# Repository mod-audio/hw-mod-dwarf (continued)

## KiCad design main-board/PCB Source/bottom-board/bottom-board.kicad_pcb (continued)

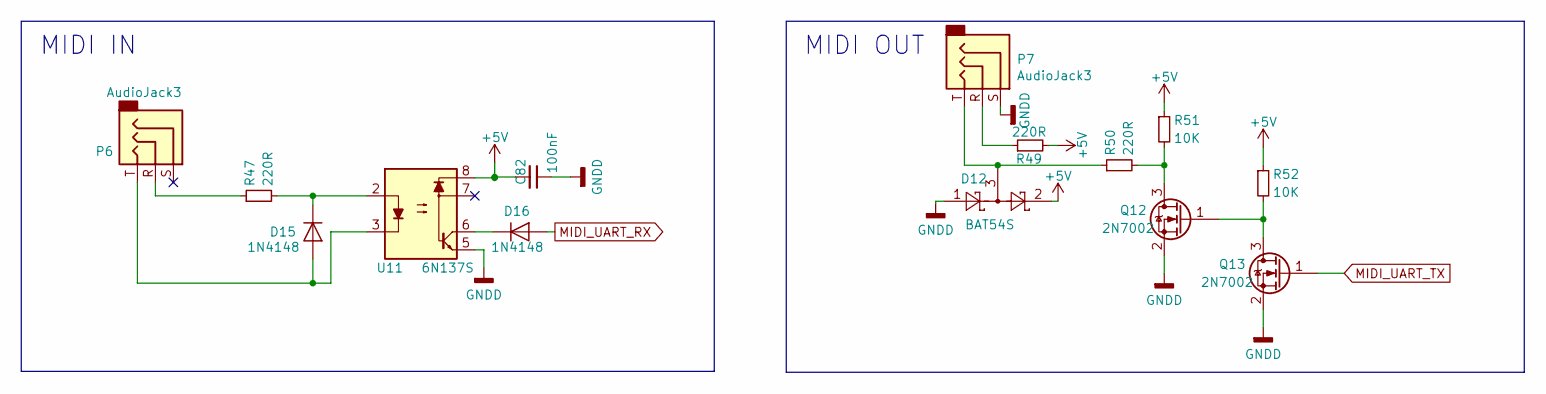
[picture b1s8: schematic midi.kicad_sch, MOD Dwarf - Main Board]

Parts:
C82: 100nF; C_0603_1608Metric; MPN GCM188R71C104KA37D
D12: BAT54S; SOT-23; MPN BAT54SFILM
D15, D16: 1N4148; D_SOD-323; MPN 1N4148WS
P6, P7: AudioJack3; Jack_3.5mm_CUI_SJ-3523-SMT_Horizontal; MPN SJ-3523-SMT-TR
Q12, Q13: 2N7002; SOT-23; MPN 2N7002P,215
R47, R49, R50: 220R; R_0603_1608Metric; MPN RC0603FR-07220RL
R51, R52: 10K; R_0603_1608Metric; MPN RR0816P-103-D
U11: 6N137S; MPN 6N137S

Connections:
+5V: C82.2, D12.2, R49.2, R51.1, R52.1, U11.8; also elsewhere on the board
GNDD: C82.1, D12.1, P7.S, Q12.2 (S), Q13.2 (S), U11.5; also elsewhere on the board
MIDI_UART_RX: D16.2 (A); also elsewhere on the board
MIDI_UART_TX: Q13.1 (G); also elsewhere on the board
unnamed: D12.3, P7.T, R50.1
unnamed: D15.1 (K), R47.2, U11.2
unnamed: D15.2 (A), P6.T, U11.3
unnamed: D16.1 (K), U11.6
unnamed: P6.R, R47.1
unnamed: P7.R, R49.1
unnamed: Q12.1 (G), Q13.3 (D), R52.2
unnamed: Q12.3 (D), R50.2, R51.2

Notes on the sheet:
MIDI OUT
MIDI IN

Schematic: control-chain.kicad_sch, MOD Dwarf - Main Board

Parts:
C54, C62: 100nF; C_0603_1608Metric; MPN GCM188R71C104KA37D
C61: 10uF; CP_Elec_4x5.7; MPN EEE-HB1C100R
P13: RJ45; Ethernet_Jack_54602-908LF; MPN 54602-908LF
R55, R56, R63: 100R; R_0603_1608Metric; MPN RT0603DRD07100RL
R57, R58: 10K; R_0603_1608Metric; MPN RR0816P-103-D
R59, R60, R61, R62: 56R; R_0603_1608Metric; MPN CRGCQ0603F56R
U12: ISL83491; SOIC-14_3.9x8.7mm_P1.27mm; MPN ISL83491IBZ

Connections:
+12V: C61.1, C62.1, P13.4, P13.5; also elsewhere on the board
CHAIN_UART_DE: R58.1, U12.4 (DE); also elsewhere on the board
CHAIN_UART_RE: R57.2, U12.3 (~RE); also elsewhere on the board
CHAIN_UART_RX: R56.2; also elsewhere on the board
CHAIN_UART_TX: R55.2; also elsewhere on the board
GNDD: C54.2, C61.2, C62.2, P13.7, P13.8, R58.2, U12.6 (GND), U12.7 (GND); also elsewhere on the board
unnamed: R55.1, U12.5 (DI)
unnamed: R56.1, U12.2 (RO)
unnamed: R59.2, U12.12 (A)
unnamed: R60.2, U12.11 (~B)
unnamed: R61.2, U12.9 (Y)
unnamed: R62.2, U12.10 (~Z)
RS485_RX+: P13.3, R59.1, R63.1
RS485_RX-: P13.6, R60.1, R63.2
RS485_TX+: P13.1, R61.1
RS485_TX-: P13.2, R62.1

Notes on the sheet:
This port is NOT used for ethernet, but for a serial protocol that includes power over the RJ-45 connector

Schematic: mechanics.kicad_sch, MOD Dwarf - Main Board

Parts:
FID1, FID2, FID3: FIDUCIAL; fiducial_in-circuit
H1, H2, H3, H4: HOLE; Hole_3.5mm
H6, H7: MountingHole_Pad; MountingHole_3.2mm_M3_DIN965_Pad; MPN 9774030243R

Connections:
GNDD: H6.1, H7.1; also elsewhere on the board

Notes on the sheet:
SOM Mounting holes

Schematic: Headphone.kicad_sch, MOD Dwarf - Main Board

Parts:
C63, C64, C65, C66: 10uF; CP_Elec_4x5.7; MPN EEE-HB1C100R
C67, C69: 10uF; C_0805_2012Metric; MPN GRM219R61E106KA12D
C68, C85, C86: 100nF; C_0603_1608Metric; MPN GCM188R71C104KA37D
C70, C71: 100uF; CP_Elec_6.3x7.7; MPN 107SML016M
D17, D18: BAT54S; SOT-23; MPN BAT54SFILM
P14: AudioJack3; Jack_3.5mm_CUI_SJ-3523-SMT_Horizontal; MPN SJ-3523-SMT-TR
Q9, Q10: MMBFJ110; SOT-23; MPN MMBFJ110
R90, R91: 1M 1%; R_0603_1608Metric; MPN RT0603BRD071ML
R92, R93: 56K; R_0603_1608Metric; MPN RMCF0603FT56K0
R94, R95: 22R; R_0603_1608Metric; MPN RMCF0603JT22R0
R96, R97: 75K 1%; R_0603_1608Metric; MPN RR0816P-753-D
R103, R104: 6R8; R_0603_1608Metric; MPN RMCF0603FT6R80
R110, R111: 1M 1%; R_0603_1608Metric; MPN DO NOT PLACE
U8: LM4811; TSSOP-10_3x3mm_P0.5mm; MPN LM4811MM/NOPB

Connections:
+5VA: C67.2, C68.1, D17.2, D18.2, Q9.1 (D), Q10.1 (D), R110.2, R111.2, U8.10 (VDD); also elsewhere on the board
CODEC_DAC_A: C63.1; also elsewhere on the board
CODEC_DAC_B: C64.1; also elsewhere on the board
GNDA: C67.1, C68.2, C69.2, C85.1, C86.1, D17.1, D18.1, P14.S, R90.1, R91.1, R92.1, R93.1, R96.1, R97.1, U8.5 (GND), U8.7 (SHDN); also elsewhere on the board
HP_CLOCK: R95.1; also elsewhere on the board
HP_VOL: R94.1; also elsewhere on the board
unnamed: C63.2, Q9.3 (G), R90.2, R111.1
unnamed: C64.2, Q10.3 (G), R91.2, R110.1
unnamed: C65.1, Q9.2 (S), R92.2
unnamed: C65.2, U8.8 (VIN2)
unnamed: C66.1, Q10.2 (S), R93.2
unnamed: C66.2, U8.2 (VIN1)
unnamed: C69.1, U8.3 (BYPASS)
unnamed: C70.1, C85.2, D17.3, U8.1 (VOUT1)
unnamed: C70.2, R96.2, R103.2
unnamed: C71.1, C86.2, D18.3, U8.9 (VOUT2)
unnamed: C71.2, R97.2, R104.1
unnamed: P14.R, R104.2
unnamed: P14.T, R103.1
unnamed: R94.2, U8.6 (UP/DN)
unnamed: R95.2, U8.4 (CLOCK)

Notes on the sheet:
Max power 105mW
LM4811 has adjustable gain of -33dB to +12dB, this is applied to the main out signal
Minimal load of 16 ohm with 0.1% THD+N

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
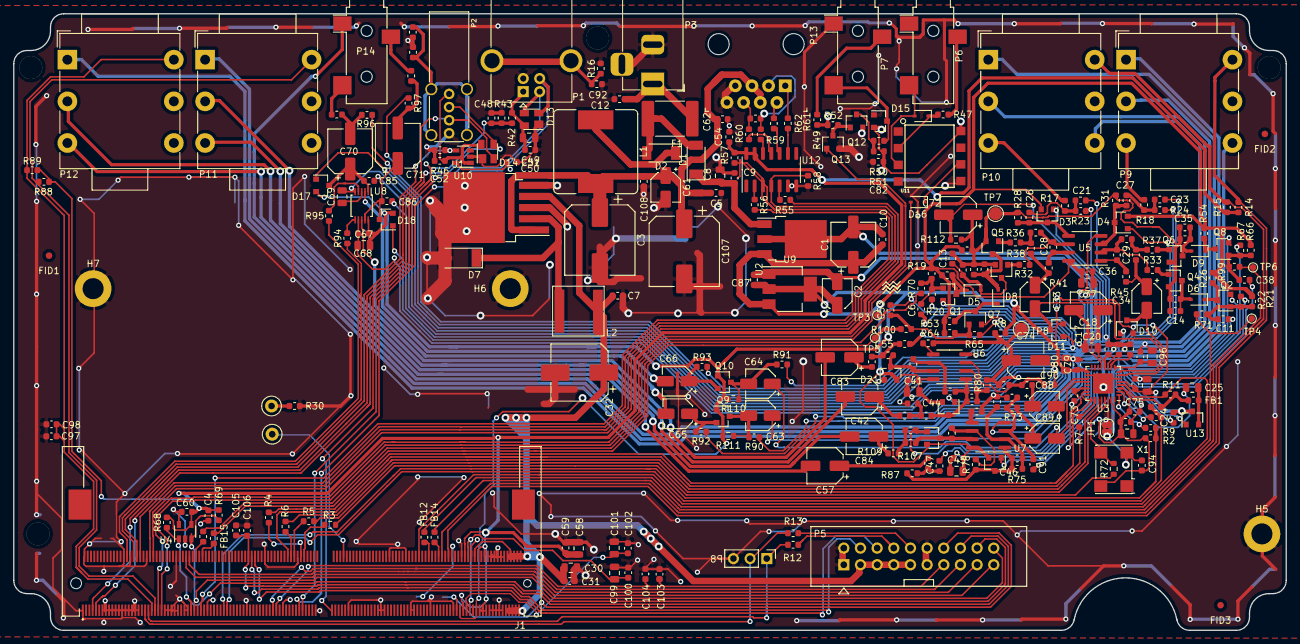
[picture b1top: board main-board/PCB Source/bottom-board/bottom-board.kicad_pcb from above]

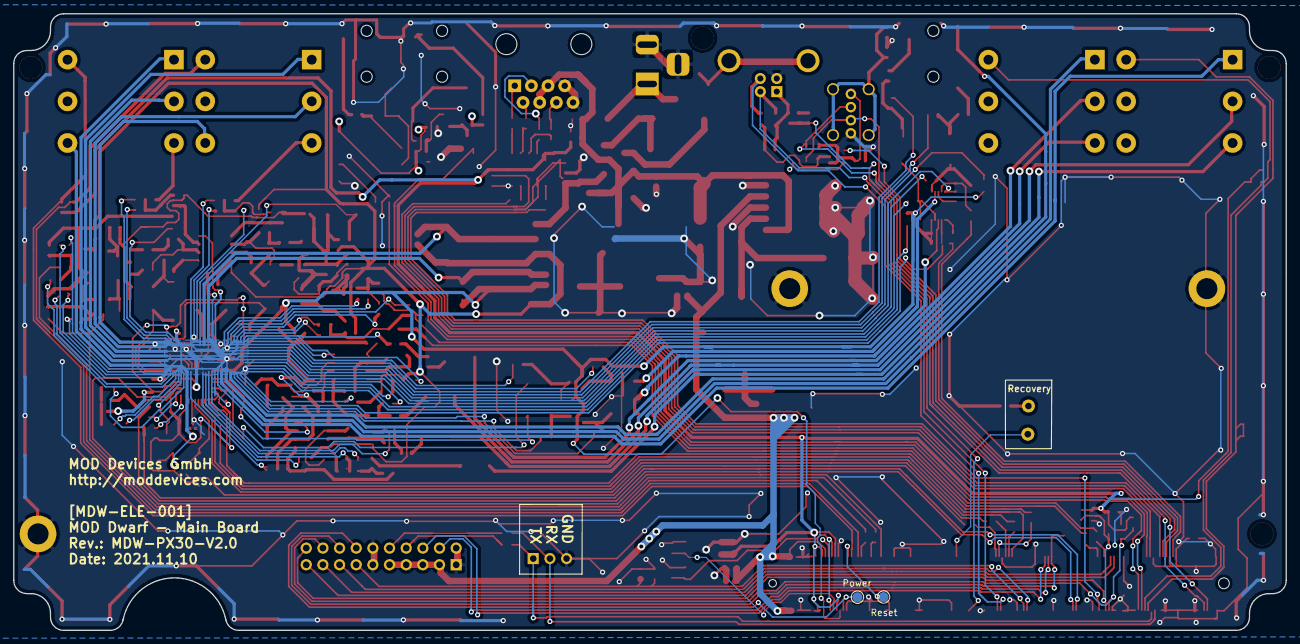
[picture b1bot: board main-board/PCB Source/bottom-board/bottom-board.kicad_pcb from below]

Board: 4 copper layers, 194.0 x 94.0 mm, 311 parts (2 on the bottom side), 179 nets.

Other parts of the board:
P5: HMI_DATA; Pin_Header_Straight_2x10_Shrouded
Power: TestPoint; TestPoint_Pad_D1.5mm
Reset: TestPoint; TestPoint_Pad_D1.5mm

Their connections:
+5V: P5.3, P5.5, P5.7, P5.9; also elsewhere on the board
GNDD: P5.1, P5.2, P5.11, P5.12; also elsewhere on the board
HMI_ISP_ENABLE: P5.13; also elsewhere on the board
HMI_RESET: P5.15; also elsewhere on the board
HMI_RFU_RX: P5.6; also elsewhere on the board
HMI_RFU_TX: P5.4; also elsewhere on the board
HMI_UART_RX: P5.19; also elsewhere on the board
HMI_UART_TX: P5.17; also elsewhere on the board
unnamed 122: P5.8; also elsewhere on the board
unnamed 123: P5.10; also elsewhere on the board
PM_LEDS_OE: P5.16; also elsewhere on the board
PM_LEDS_SCL: P5.18; also elsewhere on the board
PM_LEDS_SDA: P5.20; also elsewhere on the board
POWER_BUTTON: P5.14, Power.1; also elsewhere on the board
RESET_BUTTON: Reset.1; also elsewhere on the board

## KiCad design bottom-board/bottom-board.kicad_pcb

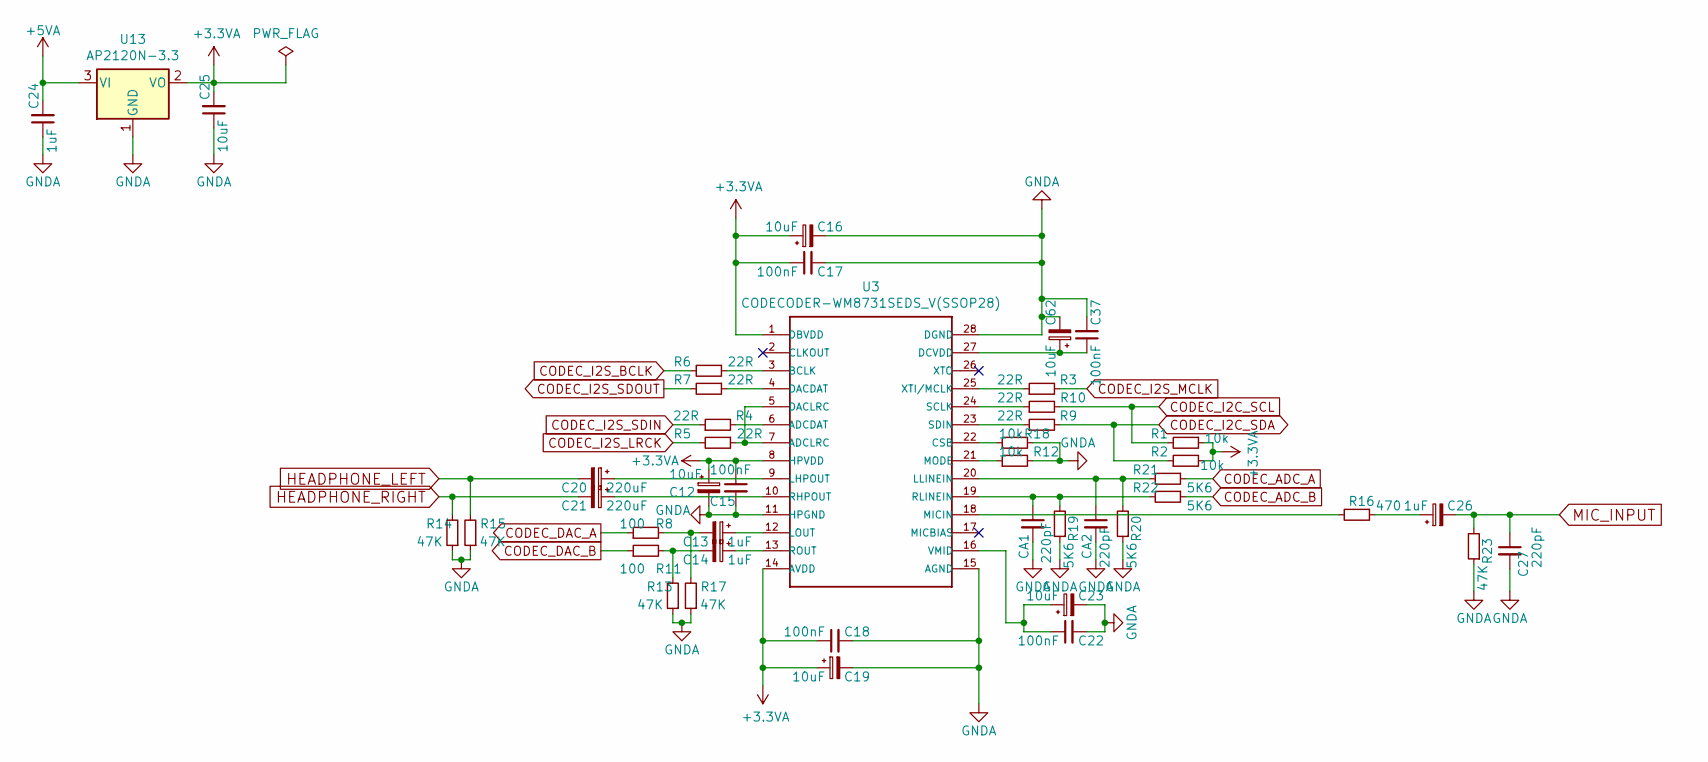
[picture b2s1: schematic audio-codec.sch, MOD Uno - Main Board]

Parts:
C12, C16, C19, C23, C62: 10uF; CP_Elec_6.3x5.3; MPN UWX1E100MCL1GB
C13, C14, C26: 1uF; CP_Elec_3x5.4
C15, C17, C18, C22, C37: 100nF; C_0402_1005Metric; MPN C1005X7R1E104K050BB
C20, C21: 220uF; CP_Elec_10x7.9
C24: 1uF; C_0805_2012Metric; MPN C2012X7R1E105K125AB
C25: 10uF; C_0805_2012Metric; MPN GRM219R61E106KA12D
C27: 220pF; C_0402_1005Metric
CA1, CA2: 220pF; C_0603_1608Metric
R1, R2, R12, R18: 10k; R_0603_1608Metric; MPN RMCF0603JT10K0
R3, R4, R5, R6, R7: 22R; R_0603_1608Metric; MPN RMCF0603JT22R0
R8, R11: 100; R_0603_1608Metric
R9, R10: 22R; R_0603_1608Metric; MPN RMCF0603JT100R
R13, R14, R15, R17, R23: 47K; R_0603_1608Metric
R16: 470; R_0603_1608Metric
R19, R20, R21, R22: 5K6; R_0603_1608Metric; MPN RMCF0603JT22R0
U3: CODECODER-WM8731SEDS_V(SSOP28); SSOP28-0.65-10.2X5.2MM
U13: AP2120N-3.3; SOT-23

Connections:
+3.3VA: C12.1, C15.1, C16.1, C17.1, C18.1, C19.1, C25.2, R1.1, R2.2, U3.1 (DBVDD), U3.8 (HPVDD), U3.14 (AVDD), U13.2 (VO)
+5VA: C24.2, U13.3 (VI); also elsewhere on the board
CODEC_ADC_A: R21.1; also elsewhere on the board
CODEC_ADC_B: R22.1; also elsewhere on the board
CODEC_DAC_A: R8.1; also elsewhere on the board
CODEC_DAC_B: R11.1; also elsewhere on the board
CODEC_I2C_SCL: R1.2, R10.2; also elsewhere on the board
CODEC_I2C_SDA: R2.1, R9.2; also elsewhere on the board
CODEC_I2S_BCLK: R6.2; also elsewhere on the board
CODEC_I2S_LRCK: R5.2; also elsewhere on the board
CODEC_I2S_MCLK: R3.2; also elsewhere on the board
CODEC_I2S_SDIN: R4.1; also elsewhere on the board
CODEC_I2S_SDOUT: R7.2; also elsewhere on the board
GNDA: C12.2, C15.2, C16.2, C17.2, C18.2, C19.2, C22.2, C23.2, C24.1, C25.1, C27.2, C37.2, C62.2, CA1.2, CA2.2, R12.2, R13.1, R14.1, R15.1, R17.1, R18.2, R19.1, R20.1, R23.1, U3.11 (HPGND), U3.15 (AGND), U3.28 (DGND), U13.1 (GND); also elsewhere on the board
HEADPHONE_LEFT: C20.2, R15.2; also elsewhere on the board
HEADPHONE_RIGHT: C21.2, R14.2; also elsewhere on the board
MIC_INPUT: C26.2, C27.1, R23.2; also elsewhere on the board
unnamed: C13.1, U3.12 (LOUT)
unnamed: C13.2, R8.2, R17.2
unnamed: C14.1, U3.13 (ROUT)
unnamed: C14.2, R11.2, R13.2
unnamed: C20.1, U3.9 (LHPOUT)
unnamed: C21.1, U3.10 (RHPOUT)
unnamed: C22.1, C23.1, U3.16 (VMID)
unnamed: C26.1, R16.1
unnamed 48: CA1.1, R19.2, R22.2, U3.19 (RLINEIN); also elsewhere on the board
unnamed 49: CA2.1, R20.2, R21.2, U3.20 (LLINEIN); also elsewhere on the board
unnamed: C37.1, C62.1, U3.27 (DCVDD)
unnamed: R3.1, U3.25 (XTI/MCLK)
unnamed: R4.2, U3.6 (ADCDAT)
unnamed: R5.1, U3.5 (DACLRC), U3.7 (ADCLRC)
unnamed: R6.1, U3.3 (BCLK)
unnamed: R7.1, U3.4 (DACDAT)
unnamed: R9.1, U3.23 (SDIN)
unnamed: R10.1, U3.24 (SCLK)
unnamed: R12.1, U3.21 (MODE)
unnamed: R16.2, U3.18 (MICIN)
unnamed: R18.1, U3.22 (CSB)

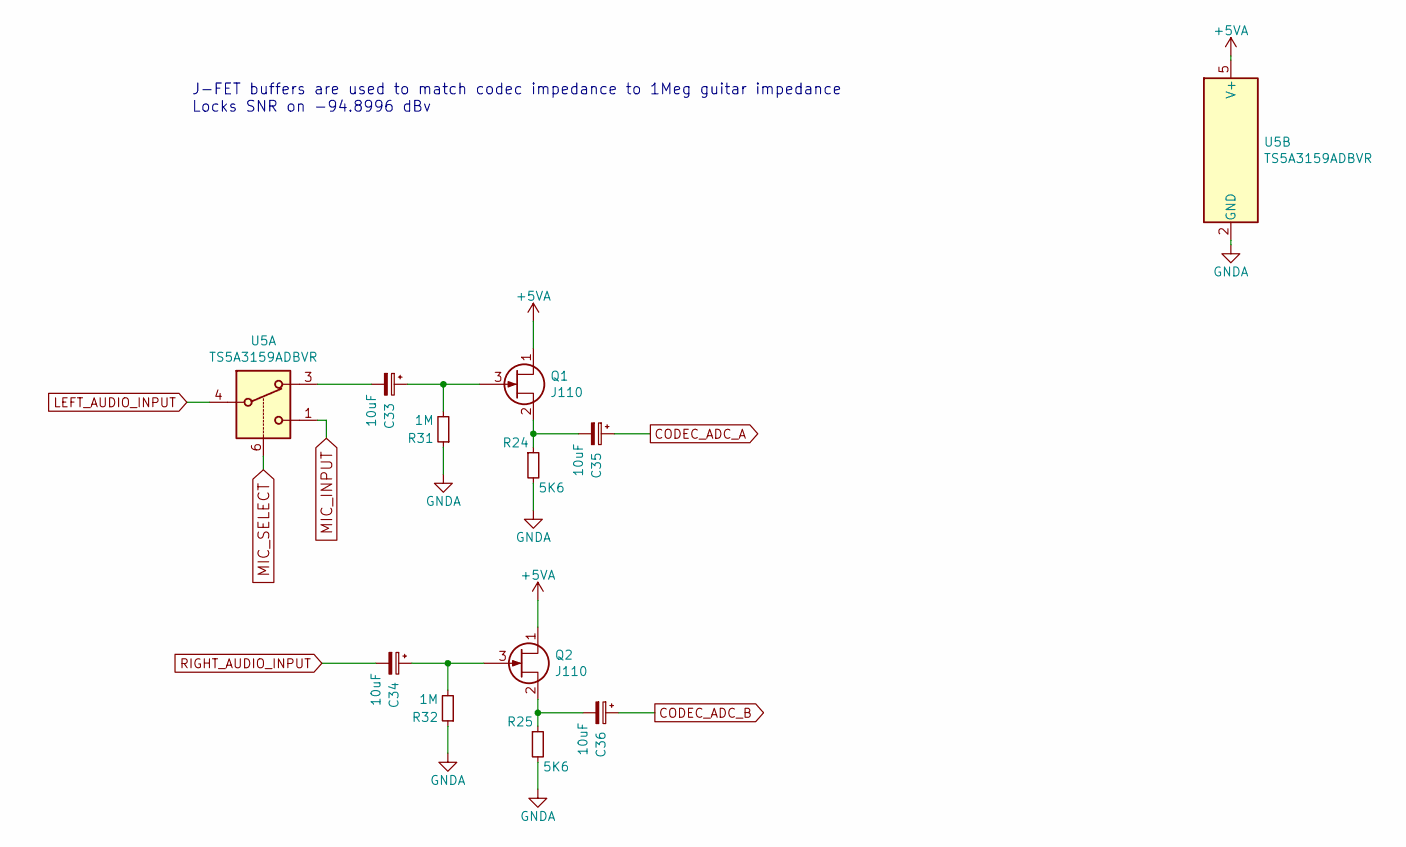
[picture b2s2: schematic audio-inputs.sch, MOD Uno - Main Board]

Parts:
C33, C34, C35, C36: 10uF; CP_Elec_5x5.3; MPN UWX1E100MCL1GB
Q1, Q2: J110; SOT-23; MPN MMBFJ110
R24, R25: 5K6; R_0603_1608Metric; MPN RMCF0603JT5K60
R31, R32: 1M; R_0603_1608Metric; MPN CPF0603B1M0E
U5: TS5A3159ADBVR; SOT-23-6; MPN TS5A3159ADBVR

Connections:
+5VA: Q1.1 (D), Q2.1 (D), U5.5 (V+); also elsewhere on the board
CODEC_ADC_A: C35.1; also elsewhere on the board
CODEC_ADC_B: C36.1; also elsewhere on the board
GNDA: R24.2, R25.2, R31.1, R32.1, U5.2 (GND); also elsewhere on the board
LEFT_AUDIO_INPUT: U5.4; also elsewhere on the board
MIC_INPUT: U5.1; also elsewhere on the board
MIC_SELECT: U5.6; also elsewhere on the board
unnamed: C33.1, Q1.3 (G), R31.2
unnamed: C33.2, U5.3
unnamed: C34.1, Q2.3 (G), R32.2
unnamed: C35.2, Q1.2 (S), R24.1
unnamed: C36.2, Q2.2 (S), R25.1
RIGHT_AUDIO_INPUT: C34.2; also elsewhere on the board

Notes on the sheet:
J-FET buffers are used to match codec impedance to 1Meg guitar impedance Locks SNR on -94.8996 dBv

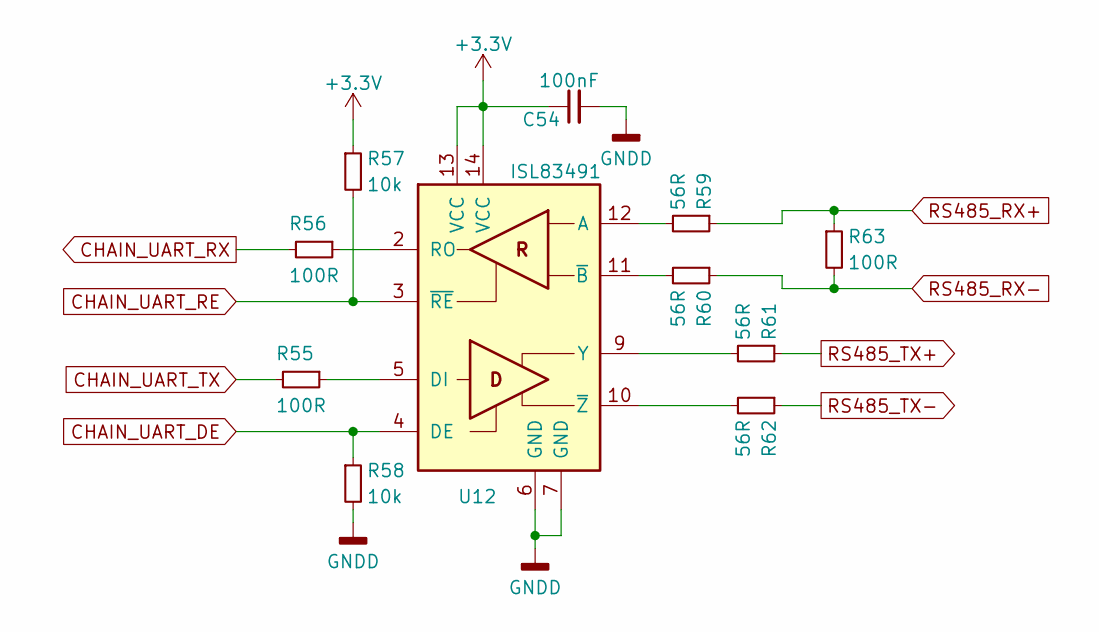
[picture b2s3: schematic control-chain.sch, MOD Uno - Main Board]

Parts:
C54: 100nF; C_0603_1608Metric; MPN C1608X7R1E104K080AA
R55, R56: 100R; R_0603_1608Metric; MPN RMCF0603JT100R
R57, R58: 10k; R_0603_1608Metric; MPN RMCF0603JT10K0
R59, R60, R61, R62: 56R; R_0603_1608Metric; MPN ERJ-P6WJ560V
R63: 100R; R_0603_1608Metric; MPN ERJ-P06J101V
U12: ISL83491; SOIC-14_3.9x8.7mm_P1.27mm; MPN ISL83491IBZ

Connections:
+3V3: C54.1, R57.1, U12.13 (VCC), U12.14 (VCC); also elsewhere on the board
CHAIN_UART_DE: R58.1, U12.4 (DE); also elsewhere on the board
CHAIN_UART_RE: R57.2, U12.3 (~RE); also elsewhere on the board
CHAIN_UART_RX: R56.2; also elsewhere on the board
CHAIN_UART_TX: R55.2; also elsewhere on the board
GNDA: C54.2, R58.2, U12.6 (GND), U12.7 (GND); also elsewhere on the board
unnamed: R55.1, U12.5 (DI)
unnamed: R56.1, U12.2 (RO)
unnamed: R59.2, U12.12 (A)
unnamed: R60.2, U12.11 (~B)
unnamed: R61.2, U12.9 (Y)
unnamed: R62.2, U12.10 (~Z~)
RS485_RX+: R59.1, R63.1; also elsewhere on the board
RS485_RX-: R60.1, R63.2; also elsewhere on the board
RS485_TX+: R61.1; also elsewhere on the board
RS485_TX-: R62.1; also elsewhere on the board

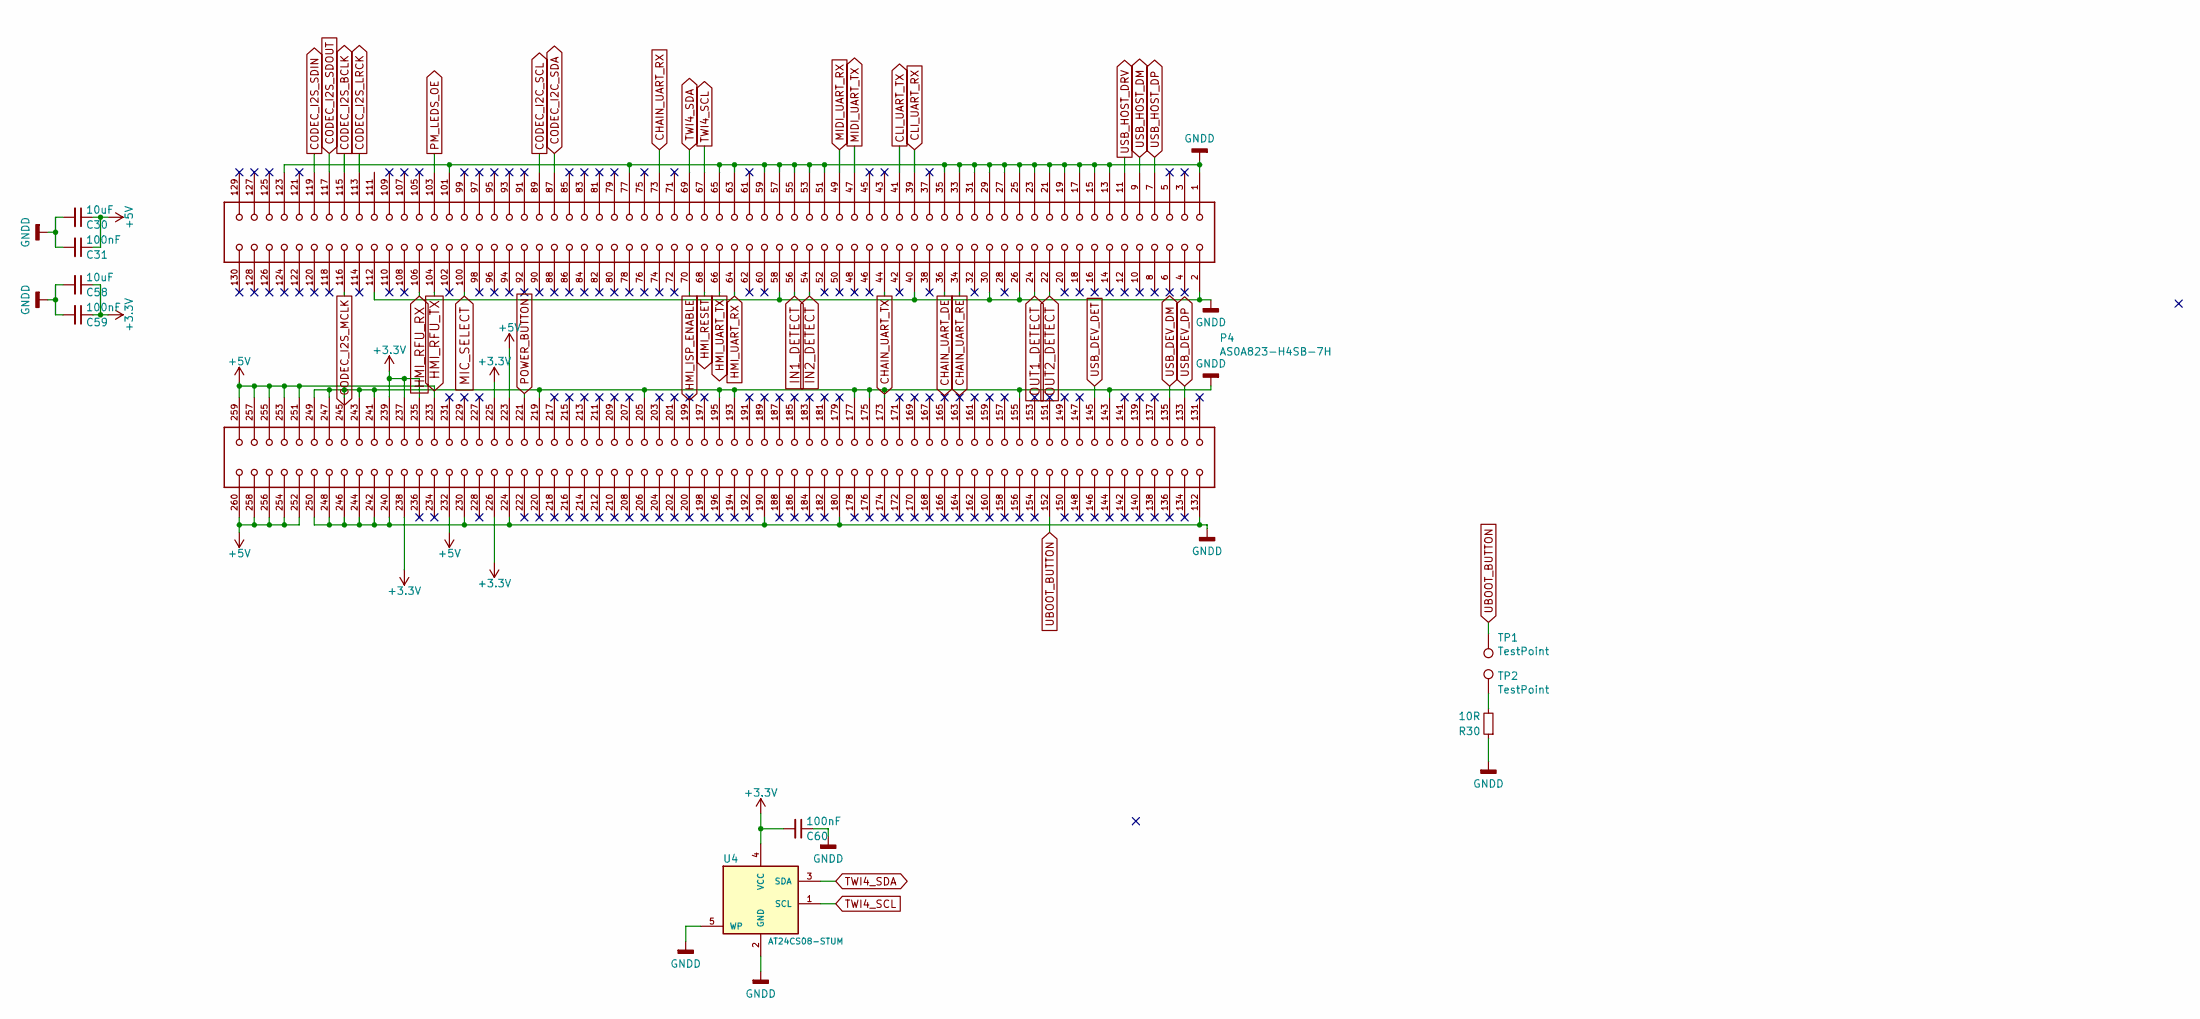
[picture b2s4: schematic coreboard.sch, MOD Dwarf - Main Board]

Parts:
C30, C58: 10uF; C_0805_2012Metric; MPN GRM219R61E106KA12D
C31, C59, C60: 100nF; C_0603_1608Metric; MPN C1608X7R1E104K080AA
P4: AS0A823-H4SB-7H; TE_2309407-1; MPN 2309407-1
R30: 10R; R_0603_1608Metric; MPN CRGCQ0603J10R
TP1, TP2: TestPoint; TestPoint_Pad_D1.5mm
U4: AT24CS08-STUM; SOT-23-5; MPN AT24CS08-STUM

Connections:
+3V3: C58.1, C59.1, C60.2, P4.225, P4.226, P4.235, P4.237, P4.238, P4.239, U4.4 (VCC); also elsewhere on the board
+5V: C30.1, C31.1, P4.223, P4.232, P4.233, P4.251, P4.252, P4.253, P4.254, P4.255, P4.256, P4.257, P4.258, P4.259, P4.260; also elsewhere on the board
CHAIN_UART_DE: P4.36; also elsewhere on the board
CHAIN_UART_RE: P4.34; also elsewhere on the board
CHAIN_UART_RX: P4.73; also elsewhere on the board
CHAIN_UART_TX: P4.44; also elsewhere on the board
CLI_UART_RX: P4.39; also elsewhere on the board
CLI_UART_TX: P4.41; also elsewhere on the board
CODEC_I2C_SCL: P4.89; also elsewhere on the board
CODEC_I2C_SDA: P4.87; also elsewhere on the board
CODEC_I2S_BCLK: P4.115; also elsewhere on the board
CODEC_I2S_LRCK: P4.113; also elsewhere on the board
CODEC_I2S_MCLK: P4.116; also elsewhere on the board
CODEC_I2S_SDIN: P4.119; also elsewhere on the board
CODEC_I2S_SDOUT: P4.117; also elsewhere on the board
GNDA: C30.2, C31.2, C58.2, C59.2, C60.1, P4.1, P4.2, P4.13, P4.15, P4.17, P4.19, P4.21, P4.23, P4.25, P4.26, P4.27, P4.29, P4.30, P4.31, P4.33, P4.35, P4.40, P4.51, P4.53, P4.55, P4.57, P4.58, P4.59, P4.63, P4.65, P4.77, P4.101, P4.112, P4.123, P4.132, P4.143, P4.155, P4.173, P4.175, P4.177, P4.180, P4.190, P4.193, P4.195, P4.205, P4.219, P4.224, P4.230, P4.240, P4.241, P4.242, P4.243, P4.244, P4.245, P4.246, P4.247, P4.248, P4.249, P4.250, R30.1, U4.2 (GND), U4.5 (WP); also elsewhere on the board
HMI_ISP_ENABLE: P4.70; also elsewhere on the board
HMI_RESET: P4.68; also elsewhere on the board
HMI_RFU_RX: P4.106; also elsewhere on the board
HMI_RFU_TX: P4.104; also elsewhere on the board
HMI_UART_RX: P4.64; also elsewhere on the board
HMI_UART_TX: P4.66; also elsewhere on the board
IN1_DETECT: P4.56; also elsewhere on the board
IN2_DETECT: P4.54; also elsewhere on the board
MIC_SELECT: P4.100; also elsewhere on the board
MIDI_UART_RX: P4.49; also elsewhere on the board
MIDI_UART_TX: P4.47; also elsewhere on the board
unnamed: R30.2, TP2.1
OUT1_DETECT: P4.24; also elsewhere on the board
OUT2_DETECT: P4.22; also elsewhere on the board
PM_LEDS_OE: P4.103; also elsewhere on the board
POWER_BUTTON: P4.221; also elsewhere on the board
TWI4_SCL: P4.67, U4.1 (SCL); also elsewhere on the board
TWI4_SDA: P4.69, U4.3 (SDA); also elsewhere on the board
UBOOT_BUTTON: P4.152, TP1.1
USB_DEV_DET: P4.145; also elsewhere on the board
USB_DEV_DM: P4.135; also elsewhere on the board
USB_DEV_DP: P4.133; also elsewhere on the board
USB_HOST_DM: P4.9; also elsewhere on the board
USB_HOST_DP: P4.7; also elsewhere on the board
USB_HOST_DRV: P4.11; also elsewhere on the board

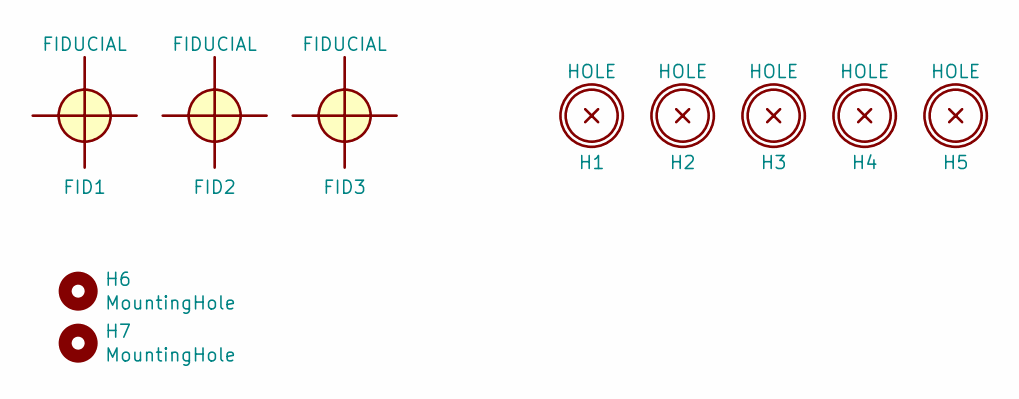
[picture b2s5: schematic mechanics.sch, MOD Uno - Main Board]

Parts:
FID1, FID2, FID3: FIDUCIAL; fiducial_in-circuit
H1, H2, H3, H4, H5: HOLE; Hole_3.5mm
H6, H7: MountingHole; MountingHole_3.2mm_M3_DIN965_Pad

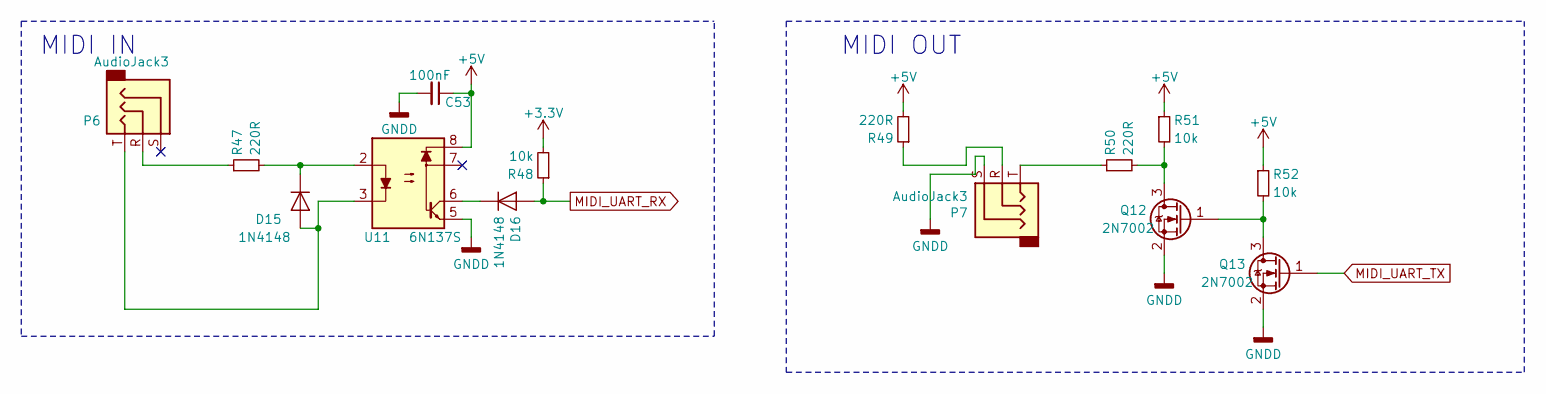
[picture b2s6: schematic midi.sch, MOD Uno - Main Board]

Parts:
C53: 100nF; C_0603_1608Metric; MPN C1608X7R1E104K080AA
D15, D16: 1N4148; D_SOD-523; MPN 1N4148X-TP
P6, P7: AudioJack3; Jack_3.5mm_CUI_SJ-3523-SMT_Horizontal; MPN SJ-3523-SMT-TR
Q12, Q13: 2N7002; SOT-23; MPN 2N7002P,215
R47, R49, R50: 220R; R_0603_1608Metric; MPN RL73N1JR22JTD
R48, R51, R52: 10k; R_0603_1608Metric; MPN RMCF0603JT10K0
U11: 6N137S; DIP-8_W7.62mm_SMDSocket_SmallPads; MPN 6N137S

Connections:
+3V3: R48.2; also elsewhere on the board
+5V: C53.1, R49.2, R51.1, R52.1, U11.8; also elsewhere on the board
GNDA: C53.2, P7.S, Q12.2 (S), Q13.2 (S), U11.5; also elsewhere on the board
MIDI_UART_RX: D16.2 (A), R48.1; also elsewhere on the board
MIDI_UART_TX: Q13.1 (G); also elsewhere on the board
unnamed: D15.1 (K), R47.2, U11.2
unnamed: D15.2 (A), P6.T, U11.3
unnamed: D16.1 (K), U11.6
unnamed: P6.R, R47.1
unnamed: P7.R, R49.1
unnamed: P7.T, R50.1
unnamed: Q12.1 (G), Q13.3 (D), R52.2
unnamed: Q12.3 (D), R50.2, R51.2

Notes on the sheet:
MIDI IN
MIDI OUT

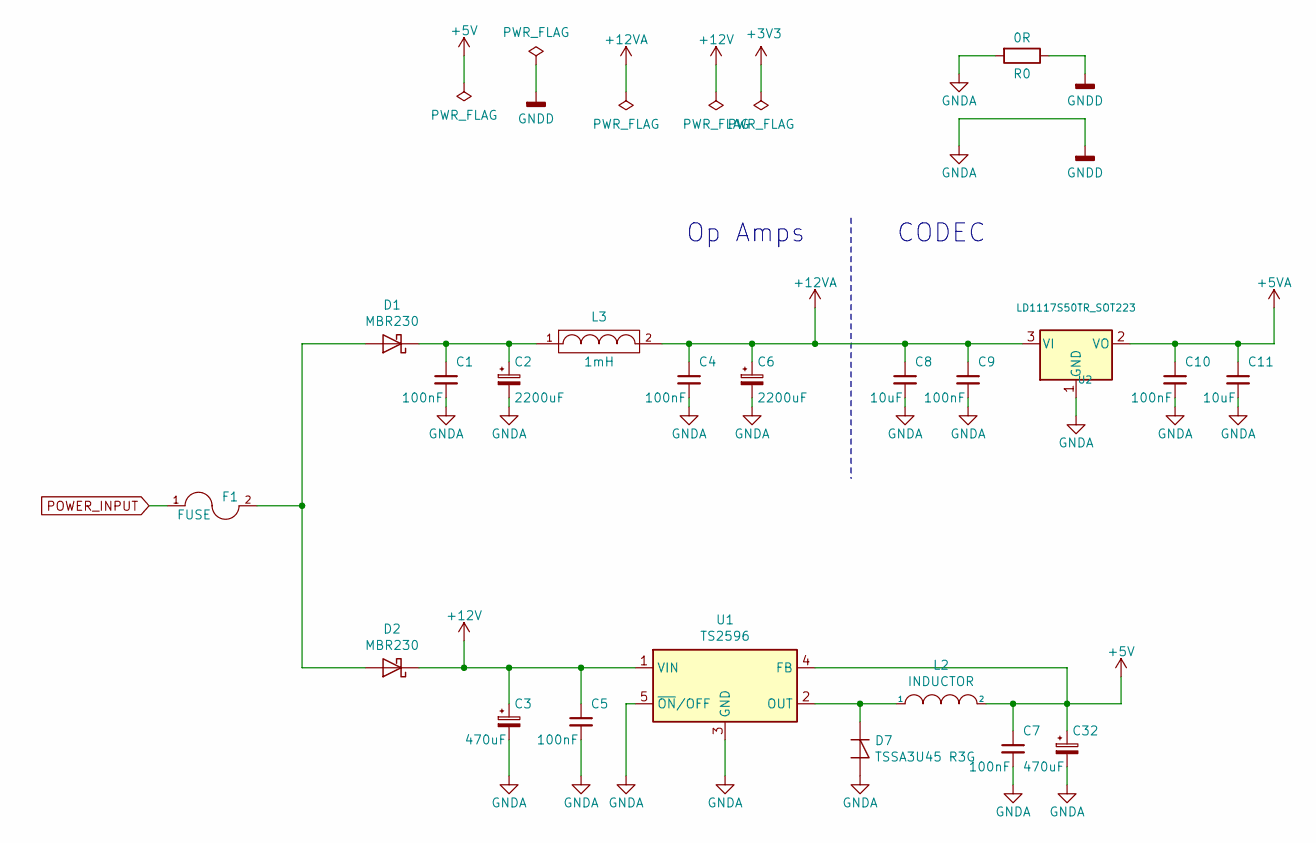
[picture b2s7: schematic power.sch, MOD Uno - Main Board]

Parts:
C1, C4, C5, C7, C9, C10: 100nF; C_0603_1608Metric; MPN C1608X7R1E104K080AA
C2, C6: 2200uF; CP_Radial_D13.0mm_P5.00mm; MPN UUG1C222MNQ6MS
C3, C32: 470uF; CP_Elec_10x7.9; MPN UWT1C471MNL1GS
C8, C11: 10uF; C_0805_2012Metric; MPN GRM219R61E106KA12D
D1, D2: MBR230; D_SOD-123F; MPN MBR230LSFT1G
D7: TSSA3U45 R3G; D_MELF; MPN TSSA3U45 R3G
F1: FUSE; Fuse_2920_7451Metric; MPN 0ZCF0200FF2C
L2: INDUCTOR; SRN8040TA; MPN SRN8040TA-470M
L3: 1mH; L_Bourns_SRR1260; MPN SRR1260-102K
R0: 0R; SolderJumper-2_P1.3mm_Bridged_Pad1.0x1.5mm
U1: TS2596; TO-263-5_TabPin3; MPN TS2596CM550 RNG
U2: LD1117S50TR_SOT223; SOT-223-3_TabPin2; MPN NCP1117DT50G

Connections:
+5V: C7.1, C32.1, L2.2, U1.4 (FB); also elsewhere on the board
+5VA: C10.1, C11.1, U2.2 (VO); also elsewhere on the board
+12V: C3.1, C5.1, D2.1 (K), U1.1 (VIN); also elsewhere on the board
+12VA: C4.1, C6.1, C8.1, C9.1, L3.2, U2.3 (VI)
GNDA: C1.2, C2.2, C3.2, C4.2, C5.2, C6.2, C7.2, C8.2, C9.2, C10.2, C11.2, C32.2, D7.2 (A), R0.1, R0.2, U1.3 (GND), U1.5 (~ON~/OFF), U2.1 (GND); also elsewhere on the board
unnamed: C1.1, C2.1, D1.1 (K), L3.1
unnamed: D1.2 (A), D2.2 (A), F1.2
unnamed: D7.1 (K), L2.1, U1.2 (OUT)
POWER_INPUT: F1.1; also elsewhere on the board

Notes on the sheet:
Op Amps
CODEC

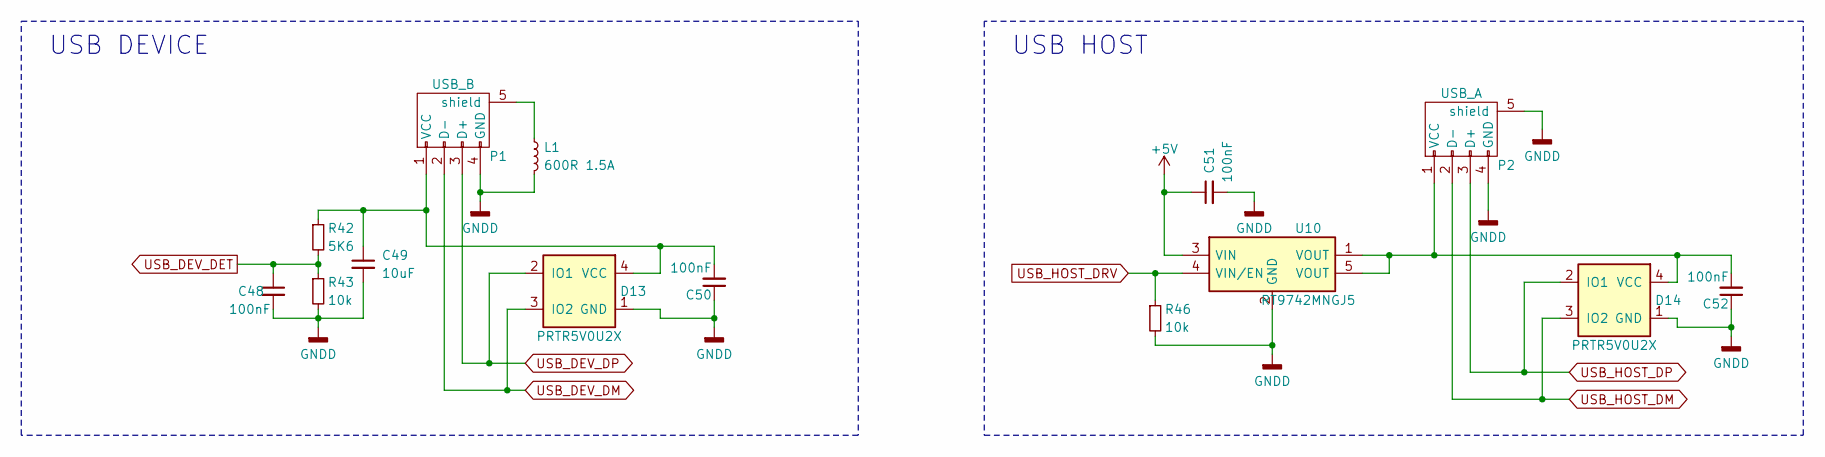
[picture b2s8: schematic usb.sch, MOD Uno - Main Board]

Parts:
C48, C50, C51, C52: 100nF; C_0603_1608Metric; MPN C1608X7R1E104K080AA
C49: 10uF; C_0805_2012Metric; MPN GRM219R61E106KA12D
D13, D14: PRTR5V0U2X; SOT-143; MPN PRTR5V0U2X,215
L1: 600R 1.5A; C_0805_2012Metric; MPN MI0805K601R-10
P1: USB_B; USB_B_OST_USB-B1HSxx_Horizontal; MPN 61729-1011BLF
P2: USB_A; USB_A_Female_Vertical_RA_73725-0110BLF; MPN 73725-0110BLF
R42: 5K6; R_0603_1608Metric; MPN RMCF0603JT5K60
R43, R46: 10k; R_0603_1608Metric; MPN RMCF0603JT10K0
U10: RT9742MNGJ5; SOT-23-5; MPN RT9742MNGJ5

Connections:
+5V: C51.1, U10.3 (VIN); also elsewhere on the board
GNDA: C48.2, C49.2, C50.1, C51.2, C52.1, D13.1 (GND), D14.1 (GND), L1.2, P1.4 (GND), P2.4 (GND), P2.5 (shield), R43.2, R46.2, U10.2 (GND); also elsewhere on the board
unnamed: C49.1, C50.2, D13.4 (VCC), P1.1 (VCC), R42.1
unnamed: C52.2, D14.4 (VCC), P2.1 (VCC), U10.1 (VOUT), U10.5 (VOUT)
unnamed: L1.1, P1.5 (shield)
USB_DEV_DET: C48.1, R42.2, R43.1; also elsewhere on the board
USB_DEV_DM: D13.3 (IO2), P1.2 (D-); also elsewhere on the board
USB_DEV_DP: D13.2 (IO1), P1.3 (D+); also elsewhere on the board
USB_HOST_DM: D14.3 (IO2), P2.2 (D-); also elsewhere on the board
USB_HOST_DP: D14.2 (IO1), P2.3 (D+); also elsewhere on the board
USB_HOST_DRV: R46.1, U10.4 (VIN/EN); also elsewhere on the board

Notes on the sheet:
USB DEVICE
USB HOST
